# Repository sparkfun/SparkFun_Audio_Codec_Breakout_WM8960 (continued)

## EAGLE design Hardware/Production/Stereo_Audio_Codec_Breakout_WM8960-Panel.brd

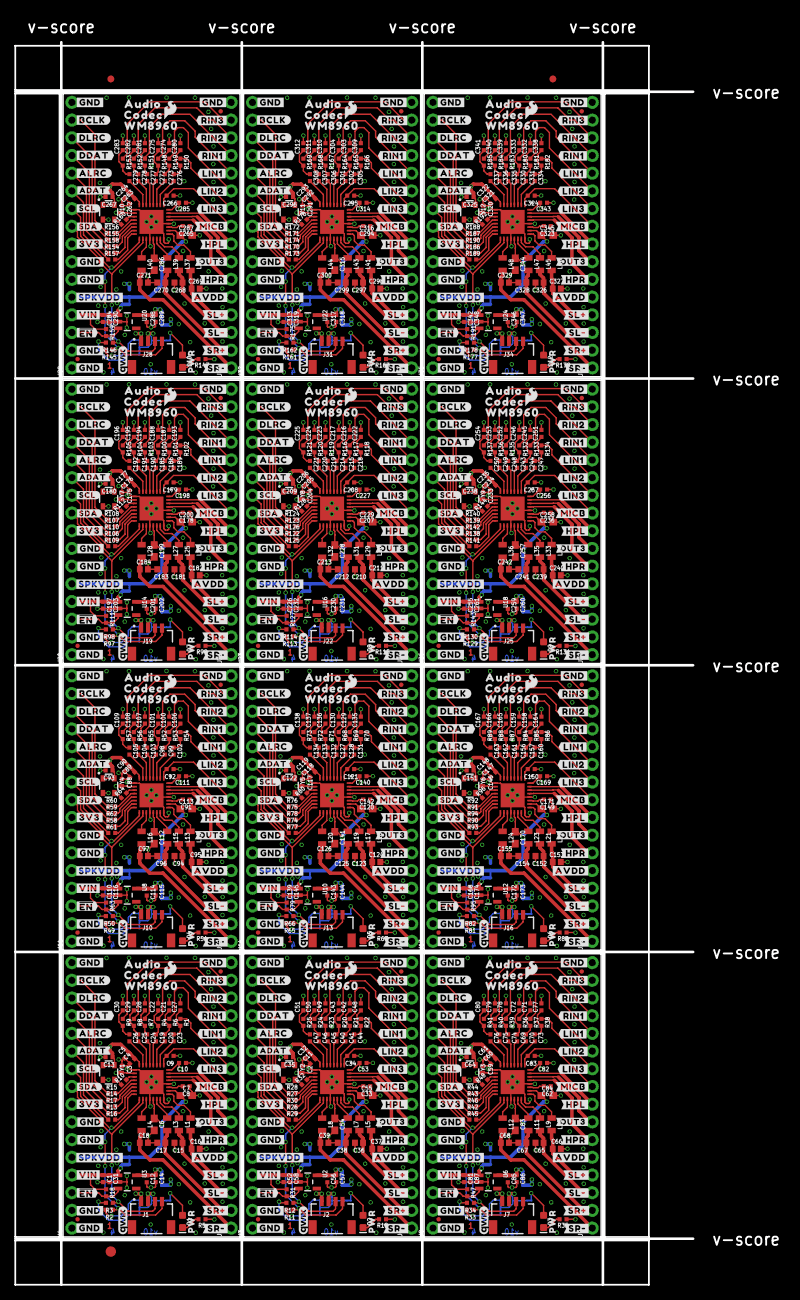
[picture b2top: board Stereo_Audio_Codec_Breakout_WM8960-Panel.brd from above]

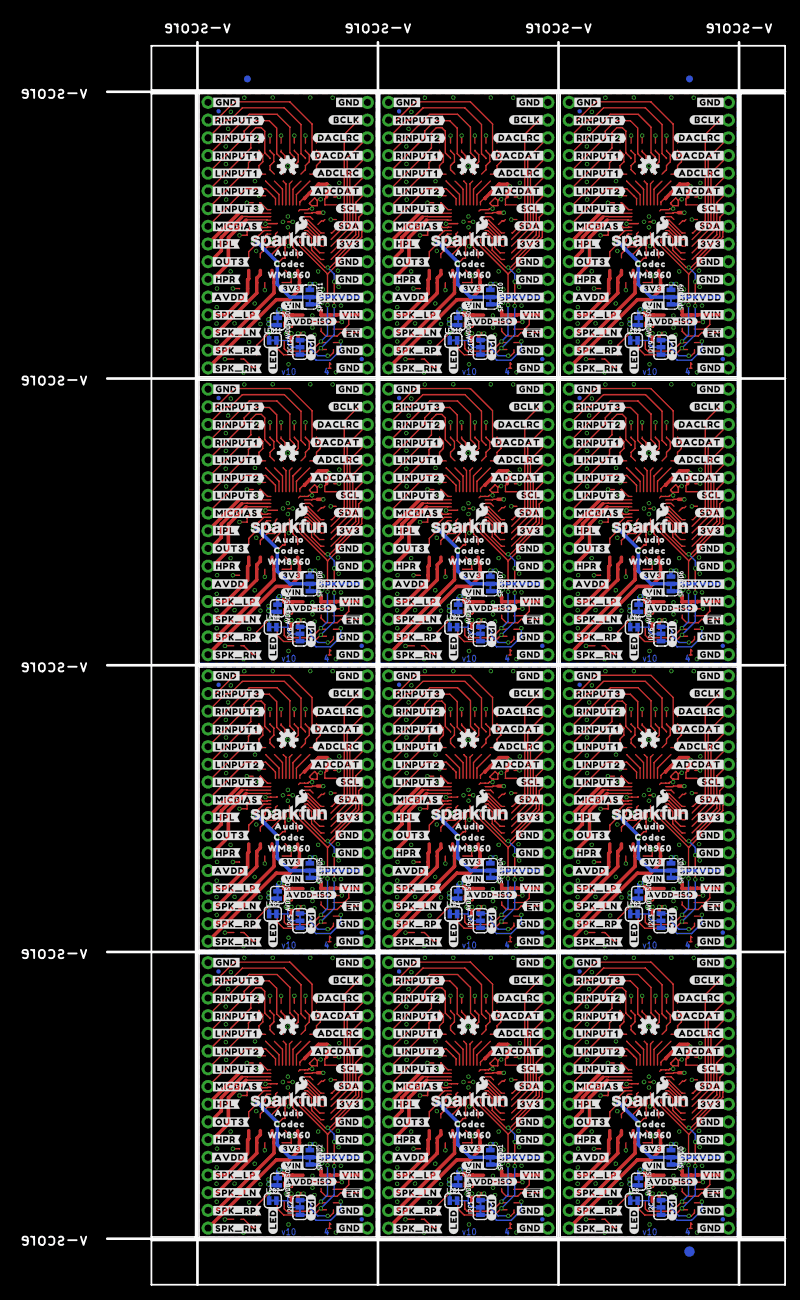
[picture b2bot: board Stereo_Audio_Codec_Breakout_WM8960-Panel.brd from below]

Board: 4 copper layers, 97.3 x 178.3 mm, 1734 parts (579 on the bottom side), 672 nets.

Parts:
AVDD-ISO, AVDD-ISO1, AVDD-ISO2, AVDD-ISO3, AVDD-ISO4, AVDD-ISO5, AVDD-ISO6, AVDD-ISO7, AVDD-ISO8, AVDD-ISO9, AVDD-ISO10, AVDD-ISO11: SMT-JUMPER_2_NC_TRACE_SILK
C1, C2, C3, C4, C5, C10, C11, C32, C52, C53, C59, C60, C61, C81, C82, C88, C89, C90, C110, C111, C117, C118, C119, C139, C140, C146, C147, C148, C168, C169, C175, C176, C177, C197, C198, C204, C205, C206, C226, C227, C233, C234, C235, C255, C256, C262, C263, C264, C284, C285, C291, C292, C293, C313, C314, C320, C321, C322, C342, C343: 0.1uF; 0402-TIGHT
C6, C7, C54, C55, C83, C84, C112, C113, C141, C142, C170, C171, C199, C200, C228, C229, C257, C258, C286, C287, C315, C316, C344, C345: 4.7uF; 0603
C8, C9, C33, C34, C62, C63, C91, C92, C120, C121, C149, C150, C178, C179, C207, C208, C236, C237, C265, C266, C294, C295, C323, C324: 4.7uF; 0402-TIGHT
C12, C19, C20, C23, C24, C25, C26, C40, C41, C44, C45, C46, C47, C56, C69, C70, C73, C74, C75, C76, C85, C98, C99, C102, C103, C104, C105, C114, C127, C128, C131, C132, C133, C134, C143, C156, C157, C160, C161, C162, C163, C172, C185, C186, C189, C190, C191, C192, C201, C214, C215, C218, C219, C220, C221, C230, C243, C244, C247, C248, C249, C250, C259, C272, C273, C276, C277, C278, C279, C288, C301, C302, C305, C306, C307, C308, C317, C330, C331, C334, C335, C336, C337, C346: 1.0uF; 0402-TIGHT
C13, C35, C64, C93, C122, C151, C180, C209, C238, C267, C296, C325: 10nF; 0402-TIGHT
C14, C31, C57, C58, C86, C87, C115, C116, C144, C145, C173, C174, C202, C203, C231, C232, C260, C261, C289, C290, C318, C319, C347, C348: 10uF; 0402-TIGHT
C15, C16, C17, C18, C36, C37, C38, C39, C65, C66, C67, C68, C94, C95, C96, C97, C123, C124, C125, C126, C152, C153, C154, C155, C181, C182, C183, C184, C210, C211, C212, C213, C239, C240, C241, C242, C268, C269, C270, C271, C297, C298, C299, C300, C326, C327, C328, C329: 1nF; 0402
C21, C22, C27, C28, C29, C30, C42, C43, C48, C49, C50, C51, C71, C72, C77, C78, C79, C80, C100, C101, C106, C107, C108, C109, C129, C130, C135, C136, C137, C138, C158, C159, C164, C165, C166, C167, C187, C188, C193, C194, C195, C196, C216, C217, C222, C223, C224, C225, C245, C246, C251, C252, C253, C254, C274, C275, C280, C281, C282, C283, C303, C304, C309, C310, C311, C312, C332, C333, C338, C339, C340, C341: 47nF; 0402-TIGHT
D1, D2, D3, D4, D5, D6, D7, D8, D9, D10, D11, D12: RED; LED-0603
E$1, E$2, E$3, E$4: FIDUCIAL-1X2
E$5, E$6: FIDUCIAL-1.5X3
FD1, FD2, FD3, FD4, FD5, FD6, FD7, FD8, FD9, FD10, FD11, FD12, FD13, FD14, FD15, FD16, FD17, FD18, FD19, FD20, FD21, FD22, FD23, FD24, FD25, FD26, FD27, FD28, FD29, FD30, FD31, FD32, FD33, FD34, FD35, FD36, FD37, FD38, FD39, FD40, FD41, FD42, FD43, FD44, FD45, FD46, FD47, FD48: FIDUCIALUFIDUCIAL; FIDUCIAL-MICRO
I2C, I2C1, I2C2, I2C3, I2C4, I2C5, I2C6, I2C7, I2C8, I2C9, I2C10, I2C11: JUMPER-SMT_3_2-NC_TRACE_SILK; SMT-JUMPER_3_2-NC_TRACE_SILK
J1, J2, J7, J10, J13, J16, J19, J22, J25, J28, J31, J34: QWIIC; JST04_1MM_RA
J3, J4, J5, J6, J8, J9, J11, J12, J14, J15, J17, J18, J20, J21, J23, J24, J26, J27, J29, J30, J32, J33, J35, J36: 1X16_NO_SILK
L1, L2, L3, L4, L5, L6, L7, L8, L9, L10, L11, L12, L13, L14, L15, L16, L17, L18, L19, L20, L21, L22, L23, L24, L25, L26, L27, L28, L29, L30, L31, L32, L33, L34, L35, L36, L37, L38, L39, L40, L41, L42, L43, L44, L45, L46, L47, L48: 220Ω; 0805
LED, LED1, LED2, LED3, LED4, LED5, LED6, LED7, LED8, LED9, LED10, LED11: SMT-JUMPER_2_NC_TRACE_SILK
LOGO1, LOGO6, LOGO9, LOGO12, LOGO15, LOGO18, LOGO21, LOGO24, LOGO27, LOGO30, LOGO33, LOGO36: SFE_LOGO_NAME_FLAME.1_INCH; SFE_LOGO_NAME_FLAME_.1
LOGO2, LOGO3, LOGO7, LOGO10, LOGO13, LOGO16, LOGO19, LOGO22, LOGO25, LOGO28, LOGO31, LOGO34: QWIIC_LOGO_4MM; QWIIC_4MM
LOGO4, LOGO5, LOGO8, LOGO11, LOGO14, LOGO17, LOGO20, LOGO23, LOGO26, LOGO29, LOGO32, LOGO35: OSHW-LOGOS; OSHW-LOGO-S
R1, R4, R6, R7, R8, R9, R20, R21, R22, R23, R24, R25, R36, R37, R38, R39, R40, R41, R52, R53, R54, R55, R56, R57, R68, R69, R70, R71, R72, R73, R84, R85, R86, R87, R88, R89, R100, R101, R102, R103, R104, R105, R116, R117, R118, R119, R120, R121, R132, R133, R134, R135, R136, R137, R148, R149, R150, R151, R152, R153, R164, R165, R166, R167, R168, R169, R180, R181, R182, R183, R184, R185: 100; 0402-TIGHT
R2, R3, R11, R12, R33, R34, R49, R50, R65, R66, R81, R82, R97, R98, R113, R114, R129, R130, R145, R146, R161, R162, R177, R178: 2.2k; 0402-TIGHT
R5, R19, R35, R51, R67, R83, R99, R115, R131, R147, R163, R179: 1k; 0402-TIGHT
R10, R13, R14, R15, R16, R17, R26, R27, R28, R29, R30, R32, R42, R43, R44, R45, R46, R48, R58, R59, R60, R61, R62, R64, R74, R75, R76, R77, R78, R80, R90, R91, R92, R93, R94, R96, R106, R107, R108, R109, R110, R112, R122, R123, R124, R125, R126, R128, R138, R139, R140, R141, R142, R144, R154, R155, R156, R157, R158, R160, R170, R171, R172, R173, R174, R176, R186, R187, R188, R189, R190, R192: 10Ω; 0402-TIGHT
R18, R31, R47, R63, R79, R95, R111, R127, R143, R159, R175, R191: 100k; 0402-TIGHT
SPKVDD, SPKVDD1, SPKVDD2, SPKVDD3, SPKVDD4, SPKVDD5, SPKVDD6, SPKVDD7, SPKVDD8, SPKVDD9, SPKVDD10, SPKVDD11: SMT-JUMPER_3_1-NC_TRACE_SILK
U1, U4, U5, U7, U9, U11, U13, U15, U17, U19, U21, U23: WM8960; QFN-32
U2, U3, U6, U8, U10, U12, U14, U16, U18, U20, U22, U24: XC6222B331MR-G; SOT23-5
U$1, U$109, U$186, U$263, U$340, U$417, U$494, U$571, U$648, U$725, U$802, U$879: AUDIO8960896055
U$2, U$110, U$187, U$264, U$341, U$418, U$495, U$572, U$649, U$726, U$803, U$880: CODEC8960896056
U$3, U$111, U$188, U$265, U$342, U$419, U$496, U$573, U$650, U$727, U$804, U$881: CODEC8960896057
U$4, U$7, U$8, U$9, U$11, U$12, U$17, U$18, U$19, U$31, U$32, U$43, U$50, U$93, U$113, U$114, U$115, U$117, U$118, U$119, U$120, U$121, U$123, U$124, U$159, U$170, U$190, U$191, U$192, U$194, U$195, U$196, U$197, U$198, U$200, U$201, U$236, U$247, U$267, U$268, U$269, U$271, U$272, U$273, U$274, U$275, U$277, U$278, U$313, U$324, U$344, U$345, U$346, U$348, U$349, U$350, U$351, U$352, U$354, U$355, U$390, U$401, U$421, U$422, U$423, U$425, U$426, U$427, U$428, U$429, U$431, U$432, U$467, U$478, U$498, U$499, U$500, U$502, U$503, U$504, U$505, U$506, U$508, U$509, U$544, U$555, U$575, U$576, U$577, U$579, U$580, U$581, U$582, U$583, U$585, U$586, U$621, U$632, U$652, U$653, U$654, U$656, U$657, U$658, U$659, U$660, U$662, U$663, U$698, U$709, U$729, U$730, U$731, U$733, U$734, U$735, U$736, U$737, U$739, U$740, U$775, U$786, U$806, U$807, U$808, U$810, U$811, U$812, U$813, U$814, U$816, U$817, U$852, U$863, U$883, U$884, U$885, U$887, U$888, U$889, U$890, U$891, U$893, U$894: #GND#8
U$5, U$145, U$222, U$299, U$376, U$453, U$530, U$607, U$684, U$761, U$838, U$915: #BCLK#0
U$6, U$13, U$155, U$232, U$309, U$386, U$463, U$540, U$617, U$694, U$771, U$848: #SR##4
U$10, U$48, U$92, U$116, U$169, U$193, U$246, U$270, U$323, U$347, U$400, U$424, U$477, U$501, U$554, U$578, U$631, U$655, U$708, U$732, U$785, U$809, U$862, U$886: #AVDD#22
U$14, U$33, U$157, U$234, U$311, U$388, U$465, U$542, U$619, U$696, U$773, U$850: #SL##6
U$15, U$25, U$156, U$233, U$310, U$387, U$464, U$541, U$618, U$695, U$772, U$849: #SR##5
U$16, U$42, U$158, U$235, U$312, U$389, U$466, U$543, U$620, U$697, U$774, U$851: #SL##7
U$20, U$134, U$211, U$288, U$365, U$442, U$519, U$596, U$673, U$750, U$827, U$904: #AVDD#ISO#0
U$21, U$135, U$212, U$289, U$366, U$443, U$520, U$597, U$674, U$751, U$828, U$905: #3V3#0
U$22, U$136, U$213, U$290, U$367, U$444, U$521, U$598, U$675, U$752, U$829, U$906: #VIN#0
U$23, U$146, U$223, U$300, U$377, U$454, U$531, U$608, U$685, U$762, U$839, U$916: #ALRC#0
U$24, U$147, U$224, U$301, U$378, U$455, U$532, U$609, U$686, U$763, U$840, U$917: #DLRC#1
U$26, U$53, U$160, U$237, U$314, U$391, U$468, U$545, U$622, U$699, U$776, U$853: #HPL#10
U$27, U$72, U$161, U$238, U$315, U$392, U$469, U$546, U$623, U$700, U$777, U$854: #HPR#11
U$28, U$51, U$73, U$94, U$162, U$171, U$239, U$248, U$316, U$325, U$393, U$402, U$470, U$479, U$547, U$556, U$624, U$633, U$701, U$710, U$778, U$787, U$855, U$864: #3V3#12
U$29, U$81, U$163, U$240, U$317, U$394, U$471, U$548, U$625, U$702, U$779, U$856: SFE_LOGO_FLAME_.1
U$30, U$64, U$107, U$122, U$184, U$199, U$261, U$276, U$338, U$353, U$415, U$430, U$492, U$507, U$569, U$584, U$646, U$661, U$723, U$738, U$800, U$815, U$877, U$892: #SPKVDD#51
U$34, U$125, U$202, U$279, U$356, U$433, U$510, U$587, U$664, U$741, U$818, U$895: ##EN##1
U$35, U$87, U$164, U$241, U$318, U$395, U$472, U$549, U$626, U$703, U$780, U$857: PWR12
U$36, U$108, U$185, U$262, U$339, U$416, U$493, U$570, U$647, U$724, U$801, U$878: WM8960896054
U$37, U$112, U$189, U$266, U$343, U$420, U$497, U$574, U$651, U$728, U$805, U$882: #OUT3#0
U$38, U$126, U$203, U$280, U$357, U$434, U$511, U$588, U$665, U$742, U$819, U$896: ##EN##2
U$39, U$88, U$165, U$242, U$319, U$396, U$473, U$550, U$627, U$704, U$781, U$858: #LED#17
U$40, U$89, U$166, U$243, U$320, U$397, U$474, U$551, U$628, U$705, U$782, U$859: #I2C#18
U$41, U$127, U$204, U$281, U$358, U$435, U$512, U$589, U$666, U$743, U$820, U$897: #OUT3#4
U$44, U$128, U$205, U$282, U$359, U$436, U$513, U$590, U$667, U$744, U$821, U$898: #RINPUT1#0
U$45, U$46, U$90, U$91, U$167, U$168, U$244, U$245, U$321, U$322, U$398, U$399, U$475, U$476, U$552, U$553, U$629, U$630, U$706, U$707, U$783, U$784, U$860, U$861: #VIN#19
U$47, U$129, U$206, U$283, U$360, U$437, U$514, U$591, U$668, U$745, U$822, U$899: #RINPUT2#0
U$49, U$130, U$207, U$284, U$361, U$438, U$515, U$592, U$669, U$746, U$823, U$900: #RINPUT3#0
U$52, U$148, U$225, U$302, U$379, U$456, U$533, U$610, U$687, U$764, U$841, U$918: #ADCLRC#2
U$54, U$139, U$216, U$293, U$370, U$447, U$524, U$601, U$678, U$755, U$832, U$909: #RIN3#0
U$55, U$149, U$226, U$303, U$380, U$457, U$534, U$611, U$688, U$765, U$842, U$919: #DACLRC#4
U$56, U$140, U$217, U$294, U$371, U$448, U$525, U$602, U$679, U$756, U$833, U$910: #RIN2#0
U$57, U$150, U$227, U$304, U$381, U$458, U$535, U$612, U$689, U$766, U$843, U$920: #BCLK#5
U$58, U$151, U$228, U$305, U$382, U$459, U$536, U$613, U$690, U$767, U$844, U$921: #ADCDAT#6
U$59, U$95, U$172, U$249, U$326, U$403, U$480, U$557, U$634, U$711, U$788, U$865: #MICB#31
U$60, U$96, U$173, U$250, U$327, U$404, U$481, U$558, U$635, U$712, U$789, U$866: WM89600
U$61, U$97, U$174, U$251, U$328, U$405, U$482, U$559, U$636, U$713, U$790, U$867: AUDIO0
U$62, U$131, U$208, U$285, U$362, U$439, U$516, U$593, U$670, U$747, U$824, U$901: #LINPUT1#0
U$63, U$132, U$209, U$286, U$363, U$440, U$517, U$594, U$671, U$748, U$825, U$902: #LINPUT2#0
U$65, U$133, U$210, U$287, U$364, U$441, U$518, U$595, U$672, U$749, U$826, U$903: #LINPUT3#0
U$66, U$137, U$214, U$291, U$368, U$445, U$522, U$599, U$676, U$753, U$830, U$907: #SCL#0
U$67, U$138, U$215, U$292, U$369, U$446, U$523, U$600, U$677, U$754, U$831, U$908: #SDA#0
U$68, U$141, U$218, U$295, U$372, U$449, U$526, U$603, U$680, U$757, U$834, U$911: #RIN1#0
U$69, U$153, U$230, U$307, U$384, U$461, U$538, U$615, U$692, U$769, U$846, U$923: #DDAT#9
U$70, U$152, U$229, U$306, U$383, U$460, U$537, U$614, U$691, U$768, U$845, U$922: #DACDAT#8
U$71, U$154, U$231, U$308, U$385, U$462, U$539, U$616, U$693, U$770, U$847, U$924: #ADAT#10
U$74, U$98, U$175, U$252, U$329, U$406, U$483, U$560, U$637, U$714, U$791, U$868: #SCL#40
U$75, U$99, U$176, U$253, U$330, U$407, U$484, U$561, U$638, U$715, U$792, U$869: #SDA#41
U$76, U$142, U$219, U$296, U$373, U$450, U$527, U$604, U$681, U$758, U$835, U$912: #LIN1#0
U$77, U$143, U$220, U$297, U$374, U$451, U$528, U$605, U$682, U$759, U$836, U$913: #LIN2#0
U$78, U$144, U$221, U$298, U$375, U$452, U$529, U$606, U$683, U$760, U$837, U$914: #LIN3#0
U$79, U$100, U$177, U$254, U$331, U$408, U$485, U$562, U$639, U$716, U$793, U$870: #MICBIAS#42
U$80, U$101, U$178, U$255, U$332, U$409, U$486, U$563, U$640, U$717, U$794, U$871: #HPL#43
U$82, U$102, U$179, U$256, U$333, U$410, U$487, U$564, U$641, U$718, U$795, U$872: #HPR#45
U$83, U$103, U$180, U$257, U$334, U$411, U$488, U$565, U$642, U$719, U$796, U$873: #SPK_LP#46
U$84, U$104, U$181, U$258, U$335, U$412, U$489, U$566, U$643, U$720, U$797, U$874: #SPK_LN#47
U$85, U$105, U$182, U$259, U$336, U$413, U$490, U$567, U$644, U$721, U$798, U$875: #SPK_RP#48
U$86, U$106, U$183, U$260, U$337, U$414, U$491, U$568, U$645, U$722, U$799, U$876: #SPK_RN#49
Y1, Y2, Y3, Y4, Y5, Y6, Y7, Y8, Y9, Y10, Y11, Y12: 24 MHz; RESONATOR-SMD-3.2X2.5

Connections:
3.3V: C3.2, C4.2, C5.2, C13.1, I2C.2, J1.2, J4.8, LED.2, SPKVDD.1, U4.8, U4.10, Y1.1, Y1.4
3.3V1: C2.2, C11.2, C32.2, C35.1, I2C1.2, J2.2, J3.8, LED1.2, SPKVDD1.1, U1.8, U1.10, Y2.1, Y2.4
3.3V2: C59.2, C60.2, C61.2, C64.1, I2C2.2, J7.2, J8.8, LED2.2, SPKVDD2.1, U5.8, U5.10, Y3.1, Y3.4
3.3V3: C88.2, C89.2, C90.2, C93.1, I2C3.2, J10.2, J11.8, LED3.2, SPKVDD3.1, U7.8, U7.10, Y4.1, Y4.4
3.3V4: C117.2, C118.2, C119.2, C122.1, I2C4.2, J13.2, J14.8, LED4.2, SPKVDD4.1, U9.8, U9.10, Y5.1, Y5.4
3.3V5: C146.2, C147.2, C148.2, C151.1, I2C5.2, J16.2, J17.8, LED5.2, SPKVDD5.1, U11.8, U11.10, Y6.1, Y6.4
3.3V6: C175.2, C176.2, C177.2, C180.1, I2C6.2, J19.2, J20.8, LED6.2, SPKVDD6.1, U13.8, U13.10, Y7.1, Y7.4
3.3V7: C204.2, C205.2, C206.2, C209.1, I2C7.2, J22.2, J23.8, LED7.2, SPKVDD7.1, U15.8, U15.10, Y8.1, Y8.4
3.3V8: C233.2, C234.2, C235.2, C238.1, I2C8.2, J25.2, J26.8, LED8.2, SPKVDD8.1, U17.8, U17.10, Y9.1, Y9.4
3.3V9: C262.2, C263.2, C264.2, C267.1, I2C9.2, J28.2, J29.8, LED9.2, SPKVDD9.1, U19.8, U19.10, Y10.1, Y10.4
3.3V10: C291.2, C292.2, C293.2, C296.1, I2C10.2, J31.2, J32.8, LED10.2, SPKVDD10.1, U21.8, U21.10, Y11.1, Y11.4
3.3V11: C320.2, C321.2, C322.2, C325.1, I2C11.2, J34.2, J35.8, LED11.2, SPKVDD11.1, U23.8, U23.10, Y12.1, Y12.4
ADCDAT: J4.11, R16.1
ADCDAT1: J3.11, R29.1
ADCDAT2: J8.11, R45.1
ADCDAT3: J11.11, R61.1
ADCDAT4: J14.11, R77.1
ADCDAT5: J17.11, R93.1
ADCDAT6: J20.11, R109.1
ADCDAT7: J23.11, R125.1
ADCDAT8: J26.11, R141.1
ADCDAT9: J29.11, R157.1
ADCDAT10: J32.11, R173.1
ADCDAT11: J35.11, R189.1
ADCLRC: J4.12, R13.1
ADCLRC1: J3.12, R26.1
ADCLRC2: J8.12, R42.1
ADCLRC3: J11.12, R58.1
ADCLRC4: J14.12, R74.1
ADCLRC5: J17.12, R90.1
ADCLRC6: J20.12, R106.1
ADCLRC7: J23.12, R122.1
ADCLRC8: J26.12, R138.1
ADCLRC9: J29.12, R154.1
ADCLRC10: J32.12, R170.1
ADCLRC11: J35.12, R186.1
AVDD: AVDD-ISO.2, C10.2, J5.5, U4.32
AVDD1: AVDD-ISO1.2, C53.2, J6.5, U1.32
AVDD2: AVDD-ISO2.2, C82.2, J9.5, U5.32
AVDD3: AVDD-ISO3.2, C111.2, J12.5, U7.32
AVDD4: AVDD-ISO4.2, C140.2, J15.5, U9.32
AVDD5: AVDD-ISO5.2, C169.2, J18.5, U11.32
AVDD6: AVDD-ISO6.2, C198.2, J21.5, U13.32
AVDD7: AVDD-ISO7.2, C227.2, J24.5, U15.32
AVDD8: AVDD-ISO8.2, C256.2, J27.5, U17.32
AVDD9: AVDD-ISO9.2, C285.2, J30.5, U19.32
AVDD10: AVDD-ISO10.2, C314.2, J33.5, U21.32
AVDD11: AVDD-ISO11.2, C343.2, J36.5, U23.32
AVDD-REG: AVDD-ISO.1, C12.1, C14.1, U3.5
AVDD-REG1: AVDD-ISO1.1, C56.1, C57.1, U2.5
AVDD-REG2: AVDD-ISO2.1, C85.1, C86.1, U6.5
AVDD-REG3: AVDD-ISO3.1, C114.1, C115.1, U8.5
AVDD-REG4: AVDD-ISO4.1, C143.1, C144.1, U10.5
AVDD-REG5: AVDD-ISO5.1, C172.1, C173.1, U12.5
AVDD-REG6: AVDD-ISO6.1, C201.1, C202.1, U14.5
AVDD-REG7: AVDD-ISO7.1, C230.1, C231.1, U16.5
AVDD-REG8: AVDD-ISO8.1, C259.1, C260.1, U18.5
AVDD-REG9: AVDD-ISO9.1, C288.1, C289.1, U20.5
AVDD-REG10: AVDD-ISO10.1, C317.1, C318.1, U22.5
AVDD-REG11: AVDD-ISO11.1, C346.1, C347.1, U24.5
BCLK: J4.15, R15.1
BCLK1: J3.15, R28.1
BCLK2: J8.15, R44.1
BCLK3: J11.15, R60.1
BCLK4: J14.15, R76.1
BCLK5: J17.15, R92.1
BCLK6: J20.15, R108.1
BCLK7: J23.15, R124.1
BCLK8: J26.15, R140.1
BCLK9: J29.15, R156.1
BCLK10: J32.15, R172.1
BCLK11: J35.15, R188.1
DACDAT: J4.13, R17.1
DACDAT1: J3.13, R30.1
DACDAT2: J8.13, R46.1
DACDAT3: J11.13, R62.1
DACDAT4: J14.13, R78.1
DACDAT5: J17.13, R94.1
DACDAT6: J20.13, R110.1
DACDAT7: J23.13, R126.1
DACDAT8: J26.13, R142.1
DACDAT9: J29.13, R158.1
DACDAT10: J32.13, R174.1
DACDAT11: J35.13, R190.1
DACLRC: J4.14, R14.1
DACLRC1: J3.14, R27.1
DACLRC2: J8.14, R43.1
DACLRC3: J11.14, R59.1
DACLRC4: J14.14, R75.1
DACLRC5: J17.14, R91.1
DACLRC6: J20.14, R107.1
DACLRC7: J23.14, R123.1
DACLRC8: J26.14, R139.1
DACLRC9: J29.14, R155.1
DACLRC10: J32.14, R171.1
DACLRC11: J35.14, R187.1
EN: J4.3, R18.2, U3.3
EN1: J3.3, R31.2, U2.3
EN2: J8.3, R47.2, U6.3
EN3: J11.3, R63.2, U8.3
EN4: J14.3, R79.2, U10.3
EN5: J17.3, R95.2, U12.3
EN6: J20.3, R111.2, U14.3
EN7: J23.3, R127.2, U16.3
EN8: J26.3, R143.2, U18.3
EN9: J29.3, R159.2, U20.3
EN10: J32.3, R175.2, U22.3
EN11: J35.3, R191.2, U24.3
GND: C1.2, C3.1, C4.1, C5.1, C6.2, C7.2, C8.1, C9.1, C10.1, C12.2, C13.2, C14.2, C15.2, C16.2, C17.2, C18.2, C21.2, C22.2, C27.2, C28.2, C29.2, C30.2, C31.2, J1.1, J4.1, J4.2, J4.6, J4.7, J4.16, J5.16, R5.1, U3.2, U4.9, U4.20, U4.24, U4.28, U4.PADDLE, Y1.2
GND1: C2.1, C11.1, C32.1, C33.1, C34.1, C35.2, C36.2, C37.2, C38.2, C39.2, C42.2, C43.2, C48.2, C49.2, C50.2, C51.2, C52.2, C53.1, C54.2, C55.2, C56.2, C57.2, C58.2, J2.1, J3.1, J3.2, J3.6, J3.7, J3.16, J6.16, R19.1, U1.9, U1.20, U1.24, U1.28, U1.PADDLE, U2.2, Y2.2
GND2: C59.1, C60.1, C61.1, C62.1, C63.1, C64.2, C65.2, C66.2, C67.2, C68.2, C71.2, C72.2, C77.2, C78.2, C79.2, C80.2, C81.2, C82.1, C83.2, C84.2, C85.2, C86.2, C87.2, J7.1, J8.1, J8.2, J8.6, J8.7, J8.16, J9.16, R35.1, U5.9, U5.20, U5.24, U5.28, U5.PADDLE, U6.2, Y3.2
GND3: C88.1, C89.1, C90.1, C91.1, C92.1, C93.2, C94.2, C95.2, C96.2, C97.2, C100.2, C101.2, C106.2, C107.2, C108.2, C109.2, C110.2, C111.1, C112.2, C113.2, C114.2, C115.2, C116.2, J10.1, J11.1, J11.2, J11.6, J11.7, J11.16, J12.16, R51.1, U7.9, U7.20, U7.24, U7.28, U7.PADDLE, U8.2, Y4.2
GND4: C117.1, C118.1, C119.1, C120.1, C121.1, C122.2, C123.2, C124.2, C125.2, C126.2, C129.2, C130.2, C135.2, C136.2, C137.2, C138.2, C139.2, C140.1, C141.2, C142.2, C143.2, C144.2, C145.2, J13.1, J14.1, J14.2, J14.6, J14.7, J14.16, J15.16, R67.1, U9.9, U9.20, U9.24, U9.28, U9.PADDLE, U10.2, Y5.2
GND5: C146.1, C147.1, C148.1, C149.1, C150.1, C151.2, C152.2, C153.2, C154.2, C155.2, C158.2, C159.2, C164.2, C165.2, C166.2, C167.2, C168.2, C169.1, C170.2, C171.2, C172.2, C173.2, C174.2, J16.1, J17.1, J17.2, J17.6, J17.7, J17.16, J18.16, R83.1, U11.9, U11.20, U11.24, U11.28, U11.PADDLE, U12.2, Y6.2
GND6: C175.1, C176.1, C177.1, C178.1, C179.1, C180.2, C181.2, C182.2, C183.2, C184.2, C187.2, C188.2, C193.2, C194.2, C195.2, C196.2, C197.2, C198.1, C199.2, C200.2, C201.2, C202.2, C203.2, J19.1, J20.1, J20.2, J20.6, J20.7, J20.16, J21.16, R99.1, U13.9, U13.20, U13.24, U13.28, U13.PADDLE, U14.2, Y7.2
GND7: C204.1, C205.1, C206.1, C207.1, C208.1, C209.2, C210.2, C211.2, C212.2, C213.2, C216.2, C217.2, C222.2, C223.2, C224.2, C225.2, C226.2, C227.1, C228.2, C229.2, C230.2, C231.2, C232.2, J22.1, J23.1, J23.2, J23.6, J23.7, J23.16, J24.16, R115.1, U15.9, U15.20, U15.24, U15.28, U15.PADDLE, U16.2, Y8.2
GND8: C233.1, C234.1, C235.1, C236.1, C237.1, C238.2, C239.2, C240.2, C241.2, C242.2, C245.2, C246.2, C251.2, C252.2, C253.2, C254.2, C255.2, C256.1, C257.2, C258.2, C259.2, C260.2, C261.2, J25.1, J26.1, J26.2, J26.6, J26.7, J26.16, J27.16, R131.1, U17.9, U17.20, U17.24, U17.28, U17.PADDLE, U18.2, Y9.2
GND9: C262.1, C263.1, C264.1, C265.1, C266.1, C267.2, C268.2, C269.2, C270.2, C271.2, C274.2, C275.2, C280.2, C281.2, C282.2, C283.2, C284.2, C285.1, C286.2, C287.2, C288.2, C289.2, C290.2, J28.1, J29.1, J29.2, J29.6, J29.7, J29.16, J30.16, R147.1, U19.9, U19.20, U19.24, U19.28, U19.PADDLE, U20.2, Y10.2
GND10: C291.1, C292.1, C293.1, C294.1, C295.1, C296.2, C297.2, C298.2, C299.2, C300.2, C303.2, C304.2, C309.2, C310.2, C311.2, C312.2, C313.2, C314.1, C315.2, C316.2, C317.2, C318.2, C319.2, J31.1, J32.1, J32.2, J32.6, J32.7, J32.16, J33.16, R163.1, U21.9, U21.20, U21.24, U21.28, U21.PADDLE, U22.2, Y11.2
GND11: C320.1, C321.1, C322.1, C323.1, C324.1, C325.2, C326.2, C327.2, C328.2, C329.2, C332.2, C333.2, C338.2, C339.2, C340.2, C341.2, C342.2, C343.1, C344.2, C345.2, C346.2, C347.2, C348.2, J34.1, J35.1, J35.2, J35.6, J35.7, J35.16, J36.16, R179.1, U23.9, U23.20, U23.24, U23.28, U23.PADDLE, U24.2, Y12.2
HP_L: J5.8, U4.31
HP_L1: J6.8, U1.31
HP_L2: J9.8, U5.31
HP_L3: J12.8, U7.31
HP_L4: J15.8, U9.31
HP_L5: J18.8, U11.31
HP_L6: J21.8, U13.31
HP_L7: J24.8, U15.31
HP_L8: J27.8, U17.31
HP_L9: J30.8, U19.31
HP_L10: J33.8, U21.31
HP_L11: J36.8, U23.31
HP_R: J5.6, U4.29
HP_R1: J6.6, U1.29
HP_R2: J9.6, U5.29
HP_R3: J12.6, U7.29
HP_R4: J15.6, U9.29
HP_R5: J18.6, U11.29
HP_R6: J21.6, U13.29
HP_R7: J24.6, U15.29
HP_R8: J27.6, U17.29
HP_R9: J30.6, U19.29
HP_R10: J33.6, U21.29
HP_R11: J36.6, U23.29
LINPUT1: J5.12, R4.1
LINPUT2: J5.11, R6.1
LINPUT3: J5.10, R1.1
LINPUT4: J6.12, R20.1
LINPUT5: J6.10, R22.1
LINPUT6: J6.11, R21.1
LINPUT7: J9.12, R36.1
LINPUT8: J9.10, R38.1
LINPUT9: J9.11, R37.1
LINPUT10: J12.12, R52.1
LINPUT11: J12.10, R54.1
LINPUT12: J12.11, R53.1
LINPUT13: J15.12, R68.1
LINPUT14: J15.10, R70.1
LINPUT15: J15.11, R69.1
LINPUT16: J18.12, R84.1
LINPUT17: J18.10, R86.1
LINPUT18: J18.11, R85.1
LINPUT19: J21.12, R100.1
LINPUT20: J21.10, R102.1
LINPUT21: J21.11, R101.1
LINPUT22: J24.12, R116.1
LINPUT23: J24.10, R118.1
LINPUT24: J24.11, R117.1
LINPUT25: J27.12, R132.1
LINPUT26: J27.10, R134.1
LINPUT27: J27.11, R133.1
LINPUT28: J30.12, R148.1
LINPUT29: J30.10, R150.1
LINPUT30: J30.11, R149.1
LINPUT31: J33.12, R164.1
LINPUT32: J33.10, R166.1
LINPUT33: J33.11, R165.1
LINPUT34: J36.12, R180.1
LINPUT35: J36.10, R182.1
LINPUT36: J36.11, R181.1
MICBIAS: C9.2, J5.9, U4.1
MICBIAS1: C34.2, J6.9, U1.1
MICBIAS2: C63.2, J9.9, U5.1
MICBIAS3: C92.2, J12.9, U7.1
MICBIAS4: C121.2, J15.9, U9.1
MICBIAS5: C150.2, J18.9, U11.1
MICBIAS6: C179.2, J21.9, U13.1
MICBIAS7: C208.2, J24.9, U15.1
MICBIAS8: C237.2, J27.9, U17.1
MICBIAS9: C266.2, J30.9, U19.1
MICBIAS10: C295.2, J33.9, U21.1
MICBIAS11: C324.2, J36.9, U23.1
unnamed: L3.1, U4.22
unnamed: R13.2, U4.15
unnamed: L4.1, U4.19
unnamed: L2.1, U4.25
unnamed: L1.1, U4.23
unnamed: D1.C, R5.2
unnamed: D1.A, LED.1
unnamed: C26.2, U4.7
unnamed: C25.2, U4.6
unnamed: C23.2, U4.2
unnamed: R10.1, Y1.3
unnamed: C20.2, U4.3
unnamed: C20.1, C21.1, R6.2
unnamed: C19.1, C22.1, R4.2
unnamed: C23.1, C27.1, R1.2
unnamed: I2C.3, R2.2
unnamed: I2C.1, R3.2
unnamed: C24.1, C28.1, R7.2
unnamed: C25.1, C29.1, R8.2
unnamed: C26.1, C30.1, R9.2
unnamed: R14.2, U4.13
unnamed: R15.2, U4.12
unnamed: R16.2, U4.16
unnamed: R17.2, U4.14
unnamed: R10.2, U4.11
unnamed: C40.2, U1.4
unnamed: C45.2, U1.5
unnamed: C33.2, U1.27
unnamed: C19.2, U4.4
unnamed: C24.2, U4.5
unnamed: I2C1.3, R11.2
unnamed: I2C1.1, R12.2
unnamed: R32.1, Y2.3
unnamed: C47.2, U1.7
unnamed: C46.2, U1.6
unnamed: C44.2, U1.2
unnamed: C41.2, U1.3
unnamed: C8.2, U4.27
unnamed: L7.1, U1.22
unnamed: L8.1, U1.19
unnamed: L6.1, U1.25
unnamed: L5.1, U1.23
unnamed: D2.C, R19.2
unnamed: C41.1, C42.1, R21.2
unnamed: C40.1, C43.1, R20.2
unnamed: C44.1, C48.1, R22.2
unnamed: C45.1, C49.1, R23.2
unnamed: C46.1, C50.1, R24.2
unnamed: C47.1, C51.1, R25.2
unnamed: R26.2, U1.15
unnamed: R27.2, U1.13
unnamed: R28.2, U1.12
unnamed: R29.2, U1.16
unnamed: R30.2, U1.14
unnamed: R32.2, U1.11
unnamed: D2.A, LED1.1
unnamed: C69.2, U5.4
unnamed: C74.2, U5.5
unnamed: C62.2, U5.27
unnamed: I2C2.3, R33.2
unnamed: I2C2.1, R34.2
unnamed: R48.1, Y3.3
unnamed: C76.2, U5.7
unnamed: C75.2, U5.6
unnamed: C73.2, U5.2
unnamed: C70.2, U5.3
unnamed: L11.1, U5.22
unnamed: L12.1, U5.19
unnamed: L10.1, U5.25
unnamed: L9.1, U5.23
unnamed: D3.C, R35.2
unnamed: C70.1, C71.1, R37.2
unnamed: C69.1, C72.1, R36.2
unnamed: C73.1, C77.1, R38.2
unnamed: C74.1, C78.1, R39.2
unnamed: C75.1, C79.1, R40.2
unnamed: C76.1, C80.1, R41.2
unnamed: R42.2, U5.15
unnamed: R43.2, U5.13
unnamed: R44.2, U5.12
unnamed: R45.2, U5.16
unnamed: R46.2, U5.14
unnamed: R48.2, U5.11
unnamed: D3.A, LED2.1
unnamed: C98.2, U7.4
unnamed: C103.2, U7.5
unnamed: C91.2, U7.27
unnamed: I2C3.3, R49.2
unnamed: I2C3.1, R50.2
unnamed: R64.1, Y4.3
unnamed: C105.2, U7.7
unnamed: C104.2, U7.6
unnamed: C102.2, U7.2
unnamed: C99.2, U7.3
unnamed: L15.1, U7.22
unnamed: L16.1, U7.19
unnamed: L14.1, U7.25
unnamed: L13.1, U7.23
unnamed: D4.C, R51.2
unnamed: C99.1, C100.1, R53.2
unnamed: C98.1, C101.1, R52.2
unnamed: C102.1, C106.1, R54.2
unnamed: C103.1, C107.1, R55.2
unnamed: C104.1, C108.1, R56.2
unnamed: C105.1, C109.1, R57.2
unnamed: R58.2, U7.15
unnamed: R59.2, U7.13
unnamed: R60.2, U7.12
unnamed: R61.2, U7.16
unnamed: R62.2, U7.14
unnamed: R64.2, U7.11
unnamed: D4.A, LED3.1
unnamed: C127.2, U9.4
unnamed: C132.2, U9.5
unnamed: C120.2, U9.27
unnamed: I2C4.3, R65.2
unnamed: I2C4.1, R66.2
unnamed: R80.1, Y5.3
unnamed: C134.2, U9.7
unnamed: C133.2, U9.6
unnamed: C131.2, U9.2
unnamed: C128.2, U9.3
unnamed: L19.1, U9.22
unnamed: L20.1, U9.19
unnamed: L18.1, U9.25
unnamed: L17.1, U9.23
unnamed: D5.C, R67.2
unnamed: C128.1, C129.1, R69.2
unnamed: C127.1, C130.1, R68.2
unnamed: C131.1, C135.1, R70.2
unnamed: C132.1, C136.1, R71.2
unnamed: C133.1, C137.1, R72.2
unnamed: C134.1, C138.1, R73.2
unnamed: R74.2, U9.15
unnamed: R75.2, U9.13
unnamed: R76.2, U9.12
unnamed: R77.2, U9.16
unnamed: R78.2, U9.14
unnamed: R80.2, U9.11
unnamed: D5.A, LED4.1
unnamed: C156.2, U11.4
unnamed: C161.2, U11.5
unnamed: C149.2, U11.27
unnamed: I2C5.3, R81.2
unnamed: I2C5.1, R82.2
unnamed: R96.1, Y6.3
unnamed: C163.2, U11.7
unnamed: C162.2, U11.6
unnamed: C160.2, U11.2
unnamed: C157.2, U11.3
unnamed: L23.1, U11.22
unnamed: L24.1, U11.19
unnamed: L22.1, U11.25
unnamed: L21.1, U11.23
unnamed: D6.C, R83.2
unnamed: C157.1, C158.1, R85.2
unnamed: C156.1, C159.1, R84.2
unnamed: C160.1, C164.1, R86.2
unnamed: C161.1, C165.1, R87.2
unnamed: C162.1, C166.1, R88.2
unnamed: C163.1, C167.1, R89.2
unnamed: R90.2, U11.15
unnamed: R91.2, U11.13
unnamed: R92.2, U11.12
unnamed: R93.2, U11.16
unnamed: R94.2, U11.14
unnamed: R96.2, U11.11
unnamed: D6.A, LED5.1
unnamed: C185.2, U13.4
unnamed: C190.2, U13.5
unnamed: C178.2, U13.27
unnamed: I2C6.3, R97.2
unnamed: I2C6.1, R98.2
unnamed: R112.1, Y7.3
unnamed: C192.2, U13.7
unnamed: C191.2, U13.6
unnamed: C189.2, U13.2
unnamed: C186.2, U13.3
unnamed: L27.1, U13.22
unnamed: L28.1, U13.19
unnamed: L26.1, U13.25
unnamed: L25.1, U13.23
unnamed: D7.C, R99.2
unnamed: C186.1, C187.1, R101.2
unnamed: C185.1, C188.1, R100.2
unnamed: C189.1, C193.1, R102.2
unnamed: C190.1, C194.1, R103.2
unnamed: C191.1, C195.1, R104.2
unnamed: C192.1, C196.1, R105.2
unnamed: R106.2, U13.15
unnamed: R107.2, U13.13
unnamed: R108.2, U13.12
unnamed: R109.2, U13.16
unnamed: R110.2, U13.14
unnamed: R112.2, U13.11
unnamed: D7.A, LED6.1
unnamed: C214.2, U15.4
unnamed: C219.2, U15.5
unnamed: C207.2, U15.27
unnamed: I2C7.3, R113.2
unnamed: I2C7.1, R114.2
unnamed: R128.1, Y8.3
unnamed: C221.2, U15.7
unnamed: C220.2, U15.6
unnamed: C218.2, U15.2
unnamed: C215.2, U15.3
unnamed: L31.1, U15.22
unnamed: L32.1, U15.19
unnamed: L30.1, U15.25
unnamed: L29.1, U15.23
unnamed: D8.C, R115.2
unnamed: C215.1, C216.1, R117.2
unnamed: C214.1, C217.1, R116.2
unnamed: C218.1, C222.1, R118.2
unnamed: C219.1, C223.1, R119.2
unnamed: C220.1, C224.1, R120.2
unnamed: C221.1, C225.1, R121.2
unnamed: R122.2, U15.15
unnamed: R123.2, U15.13
unnamed: R124.2, U15.12
unnamed: R125.2, U15.16
unnamed: R126.2, U15.14
unnamed: R128.2, U15.11
unnamed: D8.A, LED7.1
unnamed: C243.2, U17.4
unnamed: C248.2, U17.5
unnamed: C236.2, U17.27
unnamed: I2C8.3, R129.2
unnamed: I2C8.1, R130.2
unnamed: R144.1, Y9.3
unnamed: C250.2, U17.7
unnamed: C249.2, U17.6
unnamed: C247.2, U17.2
unnamed: C244.2, U17.3
unnamed: L35.1, U17.22
unnamed: L36.1, U17.19
unnamed: L34.1, U17.25
unnamed: L33.1, U17.23
unnamed: D9.C, R131.2
unnamed: C244.1, C245.1, R133.2
unnamed: C243.1, C246.1, R132.2
unnamed: C247.1, C251.1, R134.2
unnamed: C248.1, C252.1, R135.2
unnamed: C249.1, C253.1, R136.2
unnamed: C250.1, C254.1, R137.2
unnamed: R138.2, U17.15
unnamed: R139.2, U17.13
unnamed: R140.2, U17.12
unnamed: R141.2, U17.16
unnamed: R142.2, U17.14
unnamed: R144.2, U17.11
unnamed: D9.A, LED8.1
unnamed: C272.2, U19.4
unnamed: C277.2, U19.5
unnamed: C265.2, U19.27
unnamed: I2C9.3, R145.2
unnamed: I2C9.1, R146.2
unnamed: R160.1, Y10.3
unnamed: C279.2, U19.7
unnamed: C278.2, U19.6
unnamed: C276.2, U19.2
unnamed: C273.2, U19.3
unnamed: L39.1, U19.22
unnamed: L40.1, U19.19
unnamed: L38.1, U19.25
unnamed: L37.1, U19.23
unnamed: D10.C, R147.2
unnamed: C273.1, C274.1, R149.2
unnamed: C272.1, C275.1, R148.2
unnamed: C276.1, C280.1, R150.2
unnamed: C277.1, C281.1, R151.2
unnamed: C278.1, C282.1, R152.2
unnamed: C279.1, C283.1, R153.2
unnamed: R154.2, U19.15
unnamed: R155.2, U19.13
unnamed: R156.2, U19.12
unnamed: R157.2, U19.16
unnamed: R158.2, U19.14
unnamed: R160.2, U19.11
unnamed: D10.A, LED9.1
unnamed: C301.2, U21.4
unnamed: C306.2, U21.5
unnamed: C294.2, U21.27
unnamed: I2C10.3, R161.2
unnamed: I2C10.1, R162.2
unnamed: R176.1, Y11.3
unnamed: C308.2, U21.7
unnamed: C307.2, U21.6
unnamed: C305.2, U21.2
unnamed: C302.2, U21.3
unnamed: L43.1, U21.22
unnamed: L44.1, U21.19
unnamed: L42.1, U21.25
unnamed: L41.1, U21.23
unnamed: D11.C, R163.2
unnamed: C302.1, C303.1, R165.2
unnamed: C301.1, C304.1, R164.2
unnamed: C305.1, C309.1, R166.2
unnamed: C306.1, C310.1, R167.2
unnamed: C307.1, C311.1, R168.2
unnamed: C308.1, C312.1, R169.2
unnamed: R170.2, U21.15
unnamed: R171.2, U21.13
unnamed: R172.2, U21.12
unnamed: R173.2, U21.16
unnamed: R174.2, U21.14
unnamed: R176.2, U21.11
unnamed: D11.A, LED10.1
unnamed: C330.2, U23.4
unnamed: C335.2, U23.5
unnamed: C323.2, U23.27
unnamed: I2C11.3, R177.2
unnamed: I2C11.1, R178.2
unnamed: R192.1, Y12.3
unnamed: C337.2, U23.7
unnamed: C336.2, U23.6
unnamed: C334.2, U23.2
unnamed: C331.2, U23.3
unnamed: L47.1, U23.22
unnamed: L48.1, U23.19
unnamed: L46.1, U23.25
unnamed: L45.1, U23.23
unnamed: D12.C, R179.2
unnamed: C331.1, C332.1, R181.2
unnamed: C330.1, C333.1, R180.2
unnamed: C334.1, C338.1, R182.2
unnamed: C335.1, C339.1, R183.2
unnamed: C336.1, C340.1, R184.2
unnamed: C337.1, C341.1, R185.2
unnamed: R186.2, U23.15
unnamed: R187.2, U23.13
unnamed: R188.2, U23.12
unnamed: R189.2, U23.16
unnamed: R190.2, U23.14
unnamed: R192.2, U23.11
unnamed: D12.A, LED11.1
OUT1: J6.7, U1.30
OUT2: J9.7, U5.30
OUT3: J5.7, U4.30
OUT4: J12.7, U7.30
OUT5: J15.7, U9.30
OUT6: J18.7, U11.30
OUT7: J21.7, U13.30
OUT8: J24.7, U15.30
OUT9: J27.7, U17.30
OUT10: J30.7, U19.30
OUT11: J33.7, U21.30
OUT12: J36.7, U23.30
RINPUT1: J5.13, R7.1
RINPUT2: J5.14, R8.1
RINPUT3: J5.15, R9.1
RINPUT4: J6.13, R23.1
RINPUT5: J6.15, R25.1
RINPUT6: J6.14, R24.1
RINPUT7: J9.13, R39.1
RINPUT8: J9.15, R41.1
RINPUT9: J9.14, R40.1
RINPUT10: J12.13, R55.1
RINPUT11: J12.15, R57.1
RINPUT12: J12.14, R56.1
RINPUT13: J15.13, R71.1
RINPUT14: J15.15, R73.1
RINPUT15: J15.14, R72.1
RINPUT16: J18.13, R87.1
RINPUT17: J18.15, R89.1
RINPUT18: J18.14, R88.1
RINPUT19: J21.13, R103.1
RINPUT20: J21.15, R105.1
RINPUT21: J21.14, R104.1
RINPUT22: J24.13, R119.1
RINPUT23: J24.15, R121.1
RINPUT24: J24.14, R120.1
RINPUT25: J27.13, R135.1
RINPUT26: J27.15, R137.1
RINPUT27: J27.14, R136.1
RINPUT28: J30.13, R151.1
RINPUT29: J30.15, R153.1
RINPUT30: J30.14, R152.1
RINPUT31: J33.13, R167.1
RINPUT32: J33.15, R169.1
RINPUT33: J33.14, R168.1
RINPUT34: J36.13, R183.1
RINPUT35: J36.15, R185.1
RINPUT36: J36.14, R184.1
SCL: J1.4, J4.10, R2.1, U4.17
SCL1: J2.4, J3.10, R11.1, U1.17
SCL2: J7.4, J8.10, R33.1, U5.17
SCL3: J10.4, J11.10, R49.1, U7.17
SCL4: J13.4, J14.10, R65.1, U9.17
SCL5: J16.4, J17.10, R81.1, U11.17
SCL6: J19.4, J20.10, R97.1, U13.17
SCL7: J22.4, J23.10, R113.1, U15.17
SCL8: J25.4, J26.10, R129.1, U17.17
SCL9: J28.4, J29.10, R145.1, U19.17
SCL10: J31.4, J32.10, R161.1, U21.17
SCL11: J34.4, J35.10, R177.1, U23.17
SDA: J1.3, J4.9, R3.1, U4.18
SDA1: J2.3, J3.9, R12.1, U1.18
SDA2: J7.3, J8.9, R34.1, U5.18
SDA3: J10.3, J11.9, R50.1, U7.18
SDA4: J13.3, J14.9, R66.1, U9.18
SDA5: J16.3, J17.9, R82.1, U11.18
SDA6: J19.3, J20.9, R98.1, U13.18
SDA7: J22.3, J23.9, R114.1, U15.18
SDA8: J25.3, J26.9, R130.1, U17.18
SDA9: J28.3, J29.9, R146.1, U19.18
SDA10: J31.3, J32.9, R162.1, U21.18
SDA11: J34.3, J35.9, R178.1, U23.18
SPKVDD: C6.1, C7.1, J4.5, SPKVDD.2, U4.21, U4.26
SPKVDD1: C54.1, C55.1, J3.5, SPKVDD1.2, U1.21, U1.26
SPKVDD2: C83.1, C84.1, J8.5, SPKVDD2.2, U5.21, U5.26
SPKVDD3: C112.1, C113.1, J11.5, SPKVDD3.2, U7.21, U7.26
SPKVDD4: C141.1, C142.1, J14.5, SPKVDD4.2, U9.21, U9.26
SPKVDD5: C170.1, C171.1, J17.5, SPKVDD5.2, U11.21, U11.26
SPKVDD6: C199.1, C200.1, J20.5, SPKVDD6.2, U13.21, U13.26
SPKVDD7: C228.1, C229.1, J23.5, SPKVDD7.2, U15.21, U15.26
SPKVDD8: C257.1, C258.1, J26.5, SPKVDD8.2, U17.21, U17.26
SPKVDD9: C286.1, C287.1, J29.5, SPKVDD9.2, U19.21, U19.26
SPKVDD10: C315.1, C316.1, J32.5, SPKVDD10.2, U21.21, U21.26
SPKVDD11: C344.1, C345.1, J35.5, SPKVDD11.2, U23.21, U23.26
SPK_LN: C15.1, J5.3, L1.2
SPK_LN1: C36.1, J6.3, L5.2
SPK_LN2: C65.1, J9.3, L9.2
SPK_LN3: C94.1, J12.3, L13.2
SPK_LN4: C123.1, J15.3, L17.2
SPK_LN5: C152.1, J18.3, L21.2
SPK_LN6: C181.1, J21.3, L25.2
SPK_LN7: C210.1, J24.3, L29.2
SPK_LN8: C239.1, J27.3, L33.2
SPK_LN9: C268.1, J30.3, L37.2
SPK_LN10: C297.1, J33.3, L41.2
SPK_LN11: C326.1, J36.3, L45.2
SPK_LP: C16.1, J5.4, L2.2
SPK_LP1: C37.1, J6.4, L6.2
SPK_LP2: C66.1, J9.4, L10.2
SPK_LP3: C95.1, J12.4, L14.2
SPK_LP4: C124.1, J15.4, L18.2
SPK_LP5: C153.1, J18.4, L22.2
SPK_LP6: C182.1, J21.4, L26.2
SPK_LP7: C211.1, J24.4, L30.2
SPK_LP8: C240.1, J27.4, L34.2
SPK_LP9: C269.1, J30.4, L38.2
SPK_LP10: C298.1, J33.4, L42.2
SPK_LP11: C327.1, J36.4, L46.2
SPK_RN: C18.1, J5.1, L4.2
SPK_RN1: C39.1, J6.1, L8.2
SPK_RN2: C68.1, J9.1, L12.2
SPK_RN3: C97.1, J12.1, L16.2
SPK_RN4: C126.1, J15.1, L20.2
SPK_RN5: C155.1, J18.1, L24.2
SPK_RN6: C184.1, J21.1, L28.2
SPK_RN7: C213.1, J24.1, L32.2
SPK_RN8: C242.1, J27.1, L36.2
SPK_RN9: C271.1, J30.1, L40.2
SPK_RN10: C300.1, J33.1, L44.2
SPK_RN11: C329.1, J36.1, L48.2
SPK_RP: C17.1, J5.2, L3.2
SPK_RP1: C38.1, J6.2, L7.2
SPK_RP2: C67.1, J9.2, L11.2
SPK_RP3: C96.1, J12.2, L15.2
SPK_RP4: C125.1, J15.2, L19.2
SPK_RP5: C154.1, J18.2, L23.2
SPK_RP6: C183.1, J21.2, L27.2
SPK_RP7: C212.1, J24.2, L31.2
SPK_RP8: C241.1, J27.2, L35.2
SPK_RP9: C270.1, J30.2, L39.2
SPK_RP10: C299.1, J33.2, L43.2
SPK_RP11: C328.1, J36.2, L47.2
VIN: C1.1, C31.1, J4.4, R18.1, SPKVDD.3, U3.1
VIN1: C52.1, C58.1, J3.4, R31.1, SPKVDD1.3, U2.1
VIN2: C81.1, C87.1, J8.4, R47.1, SPKVDD2.3, U6.1
VIN3: C110.1, C116.1, J11.4, R63.1, SPKVDD3.3, U8.1
VIN4: C139.1, C145.1, J14.4, R79.1, SPKVDD4.3, U10.1
VIN5: C168.1, C174.1, J17.4, R95.1, SPKVDD5.3, U12.1
VIN6: C197.1, C203.1, J20.4, R111.1, SPKVDD6.3, U14.1
VIN7: C226.1, C232.1, J23.4, R127.1, SPKVDD7.3, U16.1
VIN8: C255.1, C261.1, J26.4, R143.1, SPKVDD8.3, U18.1
VIN9: C284.1, C290.1, J29.4, R159.1, SPKVDD9.3, U20.1
VIN10: C313.1, C319.1, J32.4, R175.1, SPKVDD10.3, U22.1
VIN11: C342.1, C348.1, J35.4, R191.1, SPKVDD11.3, U24.1

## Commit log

2022-08-05 initial layout idea
2022-08-05 datasheet
2022-10-06 Breakout routed ready for proto review
2022-10-06 vector font
2022-10-06 moved pwr led into sch frame
2022-10-06 Switched MONO OUT to OUT3, because that is a better name
2022-10-06 added measures
2022-10-12 Switched to single GND plane
    -moved to smaller vreg for AVDD
    -changed how power jumpers selection and isolation works
    -created 3.3V and AVDD polygons on inner layers
    -increased header length to allow for 100% analog pins to be on same side.
    -split SPKVDD decoupling cap into two separate 4.7uF caps and put near IC pins
    -added 10 ohm in series resistors on all data lines.
2022-10-12 Removed top layer GND pour
    routed GND connections to Vias
2022-10-13 checklist catches - eng run
    -Connected header pin (J4/7) to GND
    -Added 4-layer board 1/2/3/4 in copper
    -added ordering instructions
    -added Selective solder path and moved some resistors to provide clearance on medium nozzle
    -nudges some Vias to avoid cutting into silk
2022-10-13 corrected typo in sch note about I2C pullup jumper
2022-10-13 Proto Panel v01a
2022-11-18 Silk updates and codec package update
    -corrected the I2S pins to be rounded flags (because they can be inputs or outputs)
    -extended pads on codec FP to allow for better fillets. (also increased roundness of pads)
    -corrected I2C address in schematic to 0x1A
    -bumped version to v10
2022-11-18 replaced C6 and C7 to use proper SFE libraries
    -Also updated tCream on codec footprint
2022-11-18 Corrected ADCDAT and DACDAT flag ends
    ADCDAT will always be an output from the ADC.
    DACDAT will always be an input - sent from the microcontroller that is sending SD to the DAC.
2022-11-21 removing one wire stub on 3.3V off of qwiic connector
2022-11-22 Moved fiducials to avoid silk overlap
    -also increase I2C address text size in sch
2022-11-22 Production panel v10c
2022-12-15 local temp library for IC fp mod
2022-12-16 wm8960 breakout board file
    This is the full design "board" device/symbol/fp, for use as a drop into other bigger designs.
    -pretty much there, but still needs silk
